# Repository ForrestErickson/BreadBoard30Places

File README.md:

# BreadBoard30Places
Similar to a solderless bread board.

## View Schematic and PCB on Kicanvas
[BreadBoard30Places.kicad_sch](https://kicanvas.org/?github=https%3A%2F%2Fgithub.com%2FForrestErickson%2FBreadBoard30Places%2Fblob%2Fmain%2FBreadBoard30Places.kicad_sch)

[BreadBoard30Places.kicad_pcb](https://kicanvas.org/?github=https%3A%2F%2Fgithub.com%2FForrestErickson%2FBreadBoard30Places%2Fblob%2Fmain%2FBreadBoard30Places.kicad_pcb)

## 3D View from KiCad

## License
Free to and dedicated to the public domain
Free open source hardware

## Warranty
This program is designed to kill and render the earth uninhabitable, however it is not guaranteed to do so.

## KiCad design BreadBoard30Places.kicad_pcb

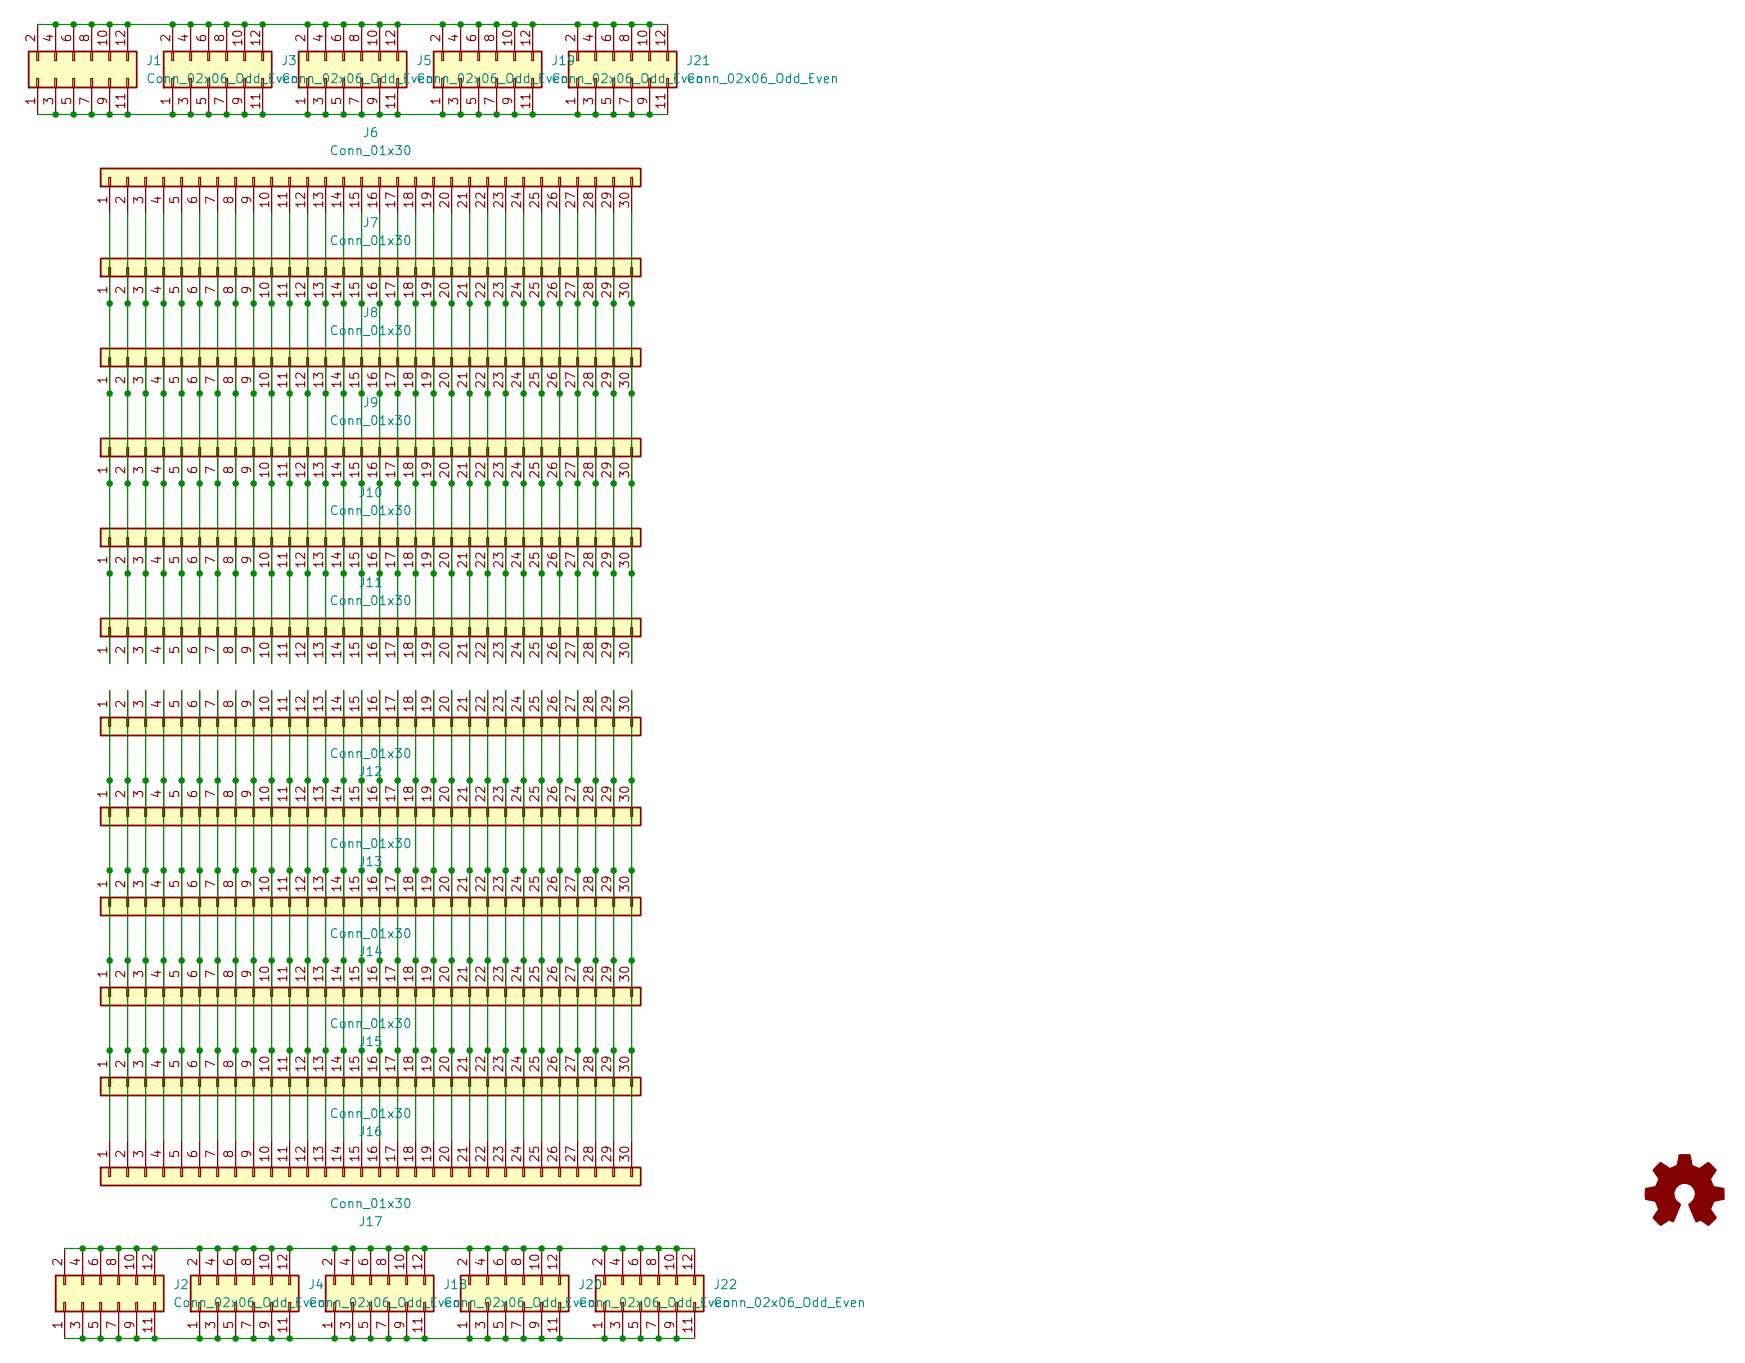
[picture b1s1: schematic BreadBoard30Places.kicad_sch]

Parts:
J1, J2, J3, J4, J5, J18, J19, J20, J21, J22: Conn_02x06_Odd_Even; PinSocket_2x06_P2.54mm_Vertical
J6, J7, J8, J9, J10, J11, J12, J13, J14, J15, J16, J17: Conn_01x30; PinSocket_1x30_P2.54mm_Vertical

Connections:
unnamed: J1.1, J1.3, J1.5, J1.7, J1.9, J1.11, J3.1, J3.3, J3.5, J3.7, J3.9, J3.11, J5.1, J5.3, J5.5, J5.7, J5.9, J5.11, J19.1, J19.3, J19.5, J19.7, J19.9, J19.11, J21.1, J21.3, J21.5, J21.7, J21.9, J21.11
unnamed: J1.2, J1.4, J1.6, J1.8, J1.10, J1.12, J3.2, J3.4, J3.6, J3.8, J3.10, J3.12, J5.2, J5.4, J5.6, J5.8, J5.10, J5.12, J19.2, J19.4, J19.6, J19.8, J19.10, J19.12, J21.2, J21.4, J21.6, J21.8, J21.10, J21.12
unnamed: J6.1, J7.1, J8.1, J9.1, J10.1, J11.1
unnamed: J6.2, J7.2, J8.2, J9.2, J10.2, J11.2
unnamed: J6.3, J7.3, J8.3, J9.3, J10.3, J11.3
unnamed: J6.4, J7.4, J8.4, J9.4, J10.4, J11.4
unnamed: J6.5, J7.5, J8.5, J9.5, J10.5, J11.5
unnamed: J6.6, J7.6, J8.6, J9.6, J10.6, J11.6
unnamed: J6.7, J7.7, J8.7, J9.7, J10.7, J11.7
unnamed: J6.8, J7.8, J8.8, J9.8, J10.8, J11.8
unnamed: J6.9, J7.9, J8.9, J9.9, J10.9, J11.9
unnamed: J6.10, J7.10, J8.10, J9.10, J10.10, J11.10
unnamed: J6.11, J7.11, J8.11, J9.11, J10.11, J11.11
unnamed: J6.12, J7.12, J8.12, J9.12, J10.12, J11.12
unnamed: J6.13, J7.13, J8.13, J9.13, J10.13, J11.13
unnamed: J6.14, J7.14, J8.14, J9.14, J10.14, J11.14
unnamed: J6.15, J7.15, J8.15, J9.15, J10.15, J11.15
unnamed: J6.16, J7.16, J8.16, J9.16, J10.16, J11.16
unnamed: J6.17, J7.17, J8.17, J9.17, J10.17, J11.17
unnamed: J6.18, J7.18, J8.18, J9.18, J10.18, J11.18
unnamed: J6.19, J7.19, J8.19, J9.19, J10.19, J11.19
unnamed: J6.20, J7.20, J8.20, J9.20, J10.20, J11.20
unnamed: J6.21, J7.21, J8.21, J9.21, J10.21, J11.21
unnamed: J6.22, J7.22, J8.22, J9.22, J10.22, J11.22
unnamed: J6.23, J7.23, J8.23, J9.23, J10.23, J11.23
unnamed: J6.24, J7.24, J8.24, J9.24, J10.24, J11.24
unnamed: J6.25, J7.25, J8.25, J9.25, J10.25, J11.25
unnamed: J6.26, J7.26, J8.26, J9.26, J10.26, J11.26
unnamed: J6.27, J7.27, J8.27, J9.27, J10.27, J11.27
unnamed: J6.28, J7.28, J8.28, J9.28, J10.28, J11.28
unnamed: J6.29, J7.29, J8.29, J9.29, J10.29, J11.29
unnamed: J6.30, J7.30, J8.30, J9.30, J10.30, J11.30
unnamed: J12.1, J13.1, J14.1, J15.1, J16.1, J17.1
unnamed: J12.2, J13.2, J14.2, J15.2, J16.2, J17.2
unnamed: J12.3, J13.3, J14.3, J15.3, J16.3, J17.3
unnamed: J12.4, J13.4, J14.4, J15.4, J16.4, J17.4
unnamed: J12.5, J13.5, J14.5, J15.5, J16.5, J17.5
unnamed: J12.6, J13.6, J14.6, J15.6, J16.6, J17.6
unnamed: J12.7, J13.7, J14.7, J15.7, J16.7, J17.7
unnamed: J12.8, J13.8, J14.8, J15.8, J16.8, J17.8
unnamed: J12.9, J13.9, J14.9, J15.9, J16.9, J17.9
unnamed: J12.10, J13.10, J14.10, J15.10, J16.10, J17.10
unnamed: J12.11, J13.11, J14.11, J15.11, J16.11, J17.11
unnamed: J12.12, J13.12, J14.12, J15.12, J16.12, J17.12
unnamed: J12.13, J13.13, J14.13, J15.13, J16.13, J17.13
unnamed: J12.14, J13.14, J14.14, J15.14, J16.14, J17.14
unnamed: J12.15, J13.15, J14.15, J15.15, J16.15, J17.15
unnamed: J12.16, J13.16, J14.16, J15.16, J16.16, J17.16
unnamed: J12.17, J13.17, J14.17, J15.17, J16.17, J17.17
unnamed: J12.18, J13.18, J14.18, J15.18, J16.18, J17.18
unnamed: J12.19, J13.19, J14.19, J15.19, J16.19, J17.19
unnamed: J12.20, J13.20, J14.20, J15.20, J16.20, J17.20
unnamed: J12.21, J13.21, J14.21, J15.21, J16.21, J17.21
unnamed: J12.22, J13.22, J14.22, J15.22, J16.22, J17.22
unnamed: J12.23, J13.23, J14.23, J15.23, J16.23, J17.23
unnamed: J12.24, J13.24, J14.24, J15.24, J16.24, J17.24
unnamed: J12.25, J13.25, J14.25, J15.25, J16.25, J17.25
unnamed: J12.26, J13.26, J14.26, J15.26, J16.26, J17.26
unnamed: J12.27, J13.27, J14.27, J15.27, J16.27, J17.27
unnamed: J12.28, J13.28, J14.28, J15.28, J16.28, J17.28
unnamed: J12.29, J13.29, J14.29, J15.29, J16.29, J17.29
unnamed: J12.30, J13.30, J14.30, J15.30, J16.30, J17.30
unnamed: J2.1, J2.3, J2.5, J2.7, J2.9, J2.11, J4.1, J4.3, J4.5, J4.7, J4.9, J4.11, J18.1, J18.3, J18.5, J18.7, J18.9, J18.11, J20.1, J20.3, J20.5, J20.7, J20.9, J20.11, J22.1, J22.3, J22.5, J22.7, J22.9, J22.11
unnamed: J2.2, J2.4, J2.6, J2.8, J2.10, J2.12, J4.2, J4.4, J4.6, J4.8, J4.10, J4.12, J18.2, J18.4, J18.6, J18.8, J18.10, J18.12, J20.2, J20.4, J20.6, J20.8, J20.10, J20.12, J22.2, J22.4, J22.6, J22.8, J22.10, J22.12

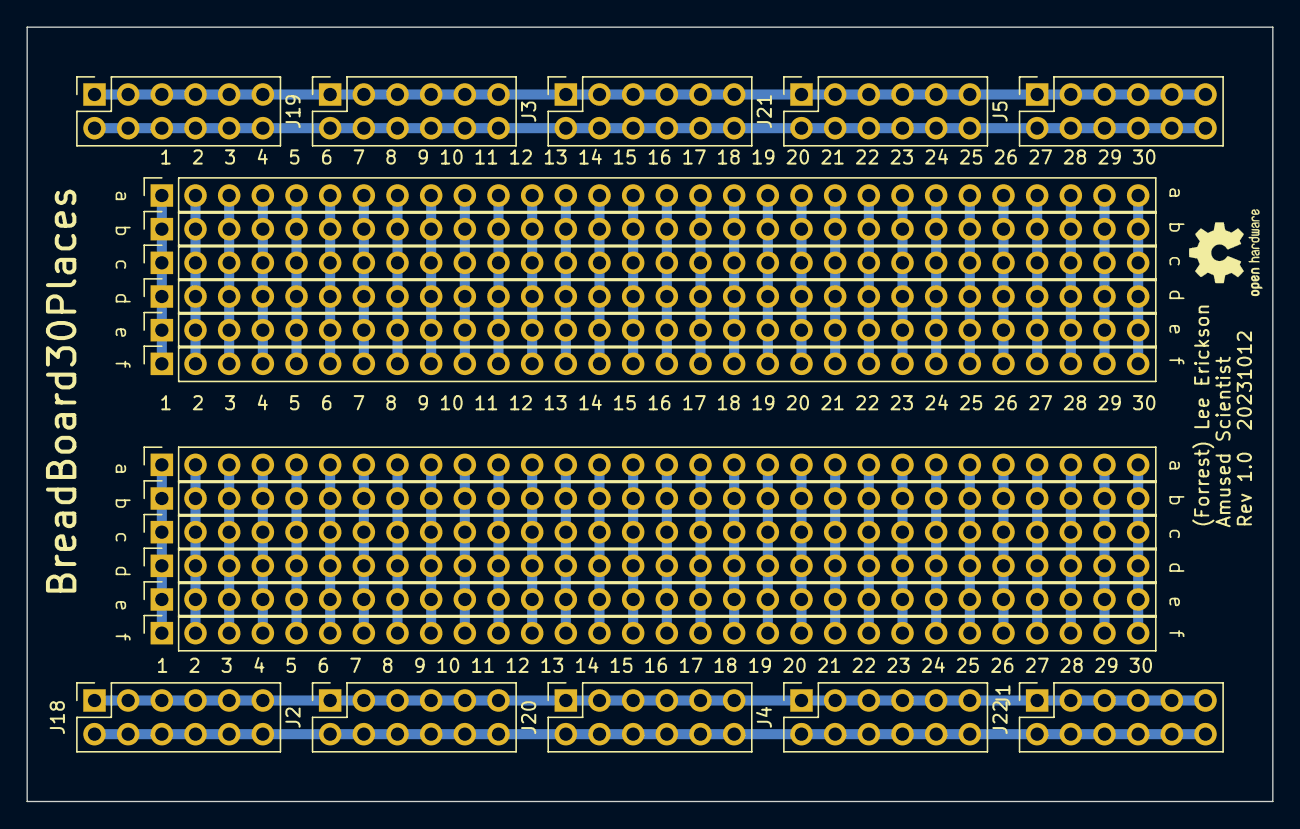
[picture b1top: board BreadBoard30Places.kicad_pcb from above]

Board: 2 copper layers, 94.0 x 58.4 mm, 22 parts (0 on the bottom side), 64 nets.

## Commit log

2023-10-13 Initial commit.
2023-10-13 Create README.md
    Add a descriptive README.md for the project.
